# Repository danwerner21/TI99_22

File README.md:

# Texas Instruments TI99/4A Clone(ish) Project

Note that this is not a fully tested project at this point. . . .

This is based Rob Krenicki's design that is based on the HackMac KiCAD schematics.  I have made several changes to the original design including:

* Placing 32K of 16bit wide fast ram on the board to fully populate the address space
* Placing an EPROM on the main board that can be used as an on-board cartridge ROM
* adding a header to allow a microcontroller to replace the GROM chips (hopefully this can be moved on-board soon)
* replacing the video DRAM with SRAM
* Updating the Keyboard header to support a soft caps lock switch on the keyboard PCB
* designing a Cherry MX keyboard
* adding headers for the GROM and expansion port to support riser cards for these ports

If there are any questions, I can be reached at vic2020Dan at gmail dot com.

## ToDo
* Cleanup/Documentation
Possible Future Thoughts:
* Redo the Board in an ATX form factor with PEB slots on board
* Add Support for the Pico9918 on-board
* Add Support for a Tang Nano FPGA TMS9918 replacement 
* Add Hex-bus port
* Add a DIN 5-pin Composite video/Audio out. 
* Add built in speech synthesis
* Clone Disk IO card
* Relocate all the ports to the back of the motherboard

* It has been suggested that we also have a console style version of the next revision as not everyone has a desire for a larger PE style machine
* Also perhaps add some keys to the keyboard

## DIP Switch Settings
The DIP switch on the main board allows one to configure which bank areas are populated with RAM.

RAM0 enables RAM to addresses >2000-3FFF (Lo Memory Expansion)
RAM1 enables RAM to addresses >A000-BFFF (Hi Memory Expansion)
RAM2 enables RAM to addresses >C000-DFFF (Hi Memory Expansion)
RAM3 enables RAM to addresses >E000-FFFF  (Hi Memory Expansion)
RAM4 enables RAM to addresses >8000-83FF (Normal TI Scratch Pad RAM)

Note that I have never actually tested off-board 8 bit RAM, so this is new territory and might need some debugging 😊   
also on-board RAM is 16 bit – so all of those external RAM sources will be slower. 

## Bugs
* on rev 0.95 R36-40 are listed as 100K ohm, they are actually 100 ohm
* on rev 0.95 the joystick and cassette connectors are mirrored and need to be mounted on the bottom side of the board to function
* Both of these are corrected in 0.96

* The reset button J1 should be attached to pin 5 of U1 not Pin 4

## Bill of Materials
### Console
Qty|Reference(s)|Part
---|------------|----
6|C1, C9, C11, C58, C73, C75|0.001uF
1|C2|22pF
3|C3, C5, C59|22uF
12|C4, C7, C13, C14, C20, C54, C55, C62, C64, C68, C71, C74|0.1uF
1|C6|1uF
7|C8, C52, C63, C65, C66, C67, C72|0.01uF
1|C10|100uF
1|C12|0.01uF
7|C15, C16, C17, C19, C21, C22, C60|100uF
30|C18, C23, C24, C25, C26, C27, C28, C29, C30, C31, C32, C33, C34, C35, C36, C37, C38, C39, C40, C41, C42, C43, C44, C45, C46, C47, C48, C49, C50, C51|0.1uF
1|C53|100uF
1|C56|12pF
1|C57|56pF
1|C61|220uF
1|C69|220pF
1|C70|0.022uF
2|CR1, CR4|1N4148
2|CR2, CR3|1N914B
1|D1|LED
1|J1|Connector PinHeader 2.54mm:PinHeader 1x02 P2.54mm Vertical
1|J2|Connector PinHeader 2.54mm:PinHeader 1x02 P2.54mm Vertical
1|J3|TerminalBlock RND:TerminalBlock RND 205-00278 1x04 P5.00mm Vertical
1|J4|Connector PinHeader 2.54mm:PinHeader 1x16 P2.54mm Vertical
2|J5, J6|Connector PinHeader 2.54mm:PinHeader 1x03 P2.54mm Vertical
1|J7|Connector PinHeader 2.54mm:PinHeader 1x03 P2.54mm Vertical
1|J8|Connector PinHeader 2.54mm:PinHeader 1x02 P2.54mm Vertical
1|J9|Connector PinHeader 2.54mm:PinHeader 1x02 P2.54mm Vertical
1|J10|Connector Dsub:DSUB-9 Female Horizontal P2.77x2.84mm EdgePinOffset4.94mm Housed MountingHolesOffset7.48mm
1|J11|Connector PinHeader 2.54mm:PinHeader 1x18 P2.54mm Vertical
1|J12|Connector PinHeader 2.54mm:PinHeader 2x22 P2.54mm Vertical
1|J13|WernerCustomLibrary:44 Pin Card Edge
1|J14|Library:CardEdge 34Pin 2.54mm Vertical
1|J15|Connector PinHeader 2.54mm:PinHeader 2x18 P2.54mm Vertical
1|J16|Connector PinSocket 2.54mm:PinSocket 1x03 P2.54mm Vertical
1|J17|Connector PinSocket 2.54mm:PinSocket 1x03 P2.54mm Vertical
1|J18|Connector Dsub:DSUB-9 Female Horizontal P2.77x2.84mm EdgePinOffset4.94mm Housed MountingHolesOffset7.48mm
1|L1|0.33uH
2|L4, L5|6.8uH
1|L7|5.8uH
1|L8|INDUCTOR (Ferrite BEAD)
7|L10, L11, L12, L13, L14, L15, L16|8.2uH
3|Q1, Q3, Q4|TIS92
1|Q2|2N3904
1|R1|150k
7|R2, R9, R11, R18, R34, R35, R46|1k
1|R3|12k
1|R4|47k
4|R5, R6, R7, R8|22
5|R10, R26, R45, R52, R53|4.7k
5|R12, R13, R14, R15, R16|1K
3|R17, R48, R50|2.2k
2|R19, R30|470
1|R20|270
1|R21|1.5k x 9 SIP bussed
1|R22|361
3|R23, R73, R75|5.6k
2|R24, R27|10
1|R25|150
1|R28|470k
1|R29|0
2|R31, R33|75
1|R32|470
4|R41, R42, R43, R44|62
1|R47|3.3k
9|R36, R37, R38, R39, R40, R49, R51, R54, R56|100
1|R55|330
1|R57|10k
1|R58|6.8k
1|R59|39k
1|R60|6.8k
4|R61, R62, R67, R68|1K
1|R63|120k
1|R64|2.7k
3|R65, R66, R76|220
1|R69|10K
1|R70|9.1k
2|R71, R72|10k
1|R74|5.6K
1|R77|15
2|RN1, RN2|10K x 9 SIP Bussed
1|SW1|DIP switchx05
1|SW2|Pin Header 01x02 Male
1|U1|TMS9904 (note this needs to be a 9904 not 9904ANL.  If the 9904ANL is used, Y1 needs to be substituted with 12Mhz, L1 needs to be substituted with 3.3uh and C2 needs to be substituted with 50pf)
1|U2|TMS9900
4|U3, U15, U22, U24|74LS04
2|U4, U9|74LS32
2|U5, U8|74LS138
1|U6|74LS03
1|U7|74LS08
3|U10, U14, U18|74LS00
2|U11, U41|74LS244
1|U12|74LS373
1|U13|74LS245
1|U16|74LS74
1|U17|74LS194
1|U19|LM2901
1|U20|LM7905 TO220
1|U21|LM2903
3|U26, U27, U28|TMC0430
3|U29, U30, U37|HM62256BLP
2|U31, U32|27C64
1|U33|SN76489
1|U34|TMS9918
3|U35, U36, U38|74LS574
1|U39|TMS9901
1|U40|74LS156
2|U42, U43|74LS367
1|U44|74LS379
1|U45|27C010
1|U46|RC4558
1|U47|74LS06
2|U48, U49|TIL119
1|Y1|48.000 MHz Crystal
1|Y2|10.7MHz Crystal

# Keyboard
Qty|Reference(s)|Value|Part
---|------------|-----|----
1|C1|0.1uF|Capacitor
1|D1|LED|LED
1|D2|LED|LED
1|J1|Pin Header 1x18 male|Pin Header 1x18 male
2|R1, R2|470 ohm|Resistor
1|R3|1K ohm|Resistor
48|SW1-SW48|Mechanical Switch|Cherry MX Switch (or compatible)
1|U1|ATtiny13A-P|IC
1|U2|74LS125|IC
3||Switch Stabilizer 2.25|
1||Switch Stabilizer 6.25|
1||Optional Alignment frame (will need modified)|
|||
|Stabilizers (frame not used):|https://www.amazon.com/Genuine-Cherry-PCB-Snap-Stabilizers/dp/B085T8QZJC|
|Stabilizers (Frame used)|https://www.amazon.com/dp/B082X4V9VC|
|Frame:|https://www.amazon.com/gp/product/B07MMB33WG|

# Cartridge Riser
Qty|Reference(s)|Part|Type
---|------------|----|----
1|J1|Pin Header 01x18 Male|Pin Header 01x18 Male
1|J2|36 Pin Edge Connector|CONN EDGE DUAL FMALE 36POS 0.100 spacing

# IO Riser
Qty|Reference(s)|Part|Type
---|------------|----|----
1|J1|Pin Header 2x22 Male|Pin Header 2x22 Male

# UNICORN BOARD
Qty|Reference(s)|Part|Type
---|------------|----|----
1|J1|Pin Header Socket 01x16 Female Right Angle|Pin Header Socket 01x16 Female Right Angle
4|U1-U4|Level Shifter|https://www.amazon.com/KeeYees-Channels-Converter-Bi-Directional-Shifter/dp/B07LG646VS
1|U5|ESP32 Devkit|https://www.amazon.com/Development-Microcontroller-Integrated-Antenna-Amplifiers/dp/B09GK74F7N

## License

The original project was licensed under the Creative Commons - Attribution - ShareAlike 3.0 License

## Attribution

This board was derrived from works by, uses design elements from, or contains sofware writen by the following:
* Rob Krenicki (https://github.com/rkrenicki/TI99-Motherboard)
* HackMac (https://bitbucket.org/hackmac/ti-schematics/wiki/Home)

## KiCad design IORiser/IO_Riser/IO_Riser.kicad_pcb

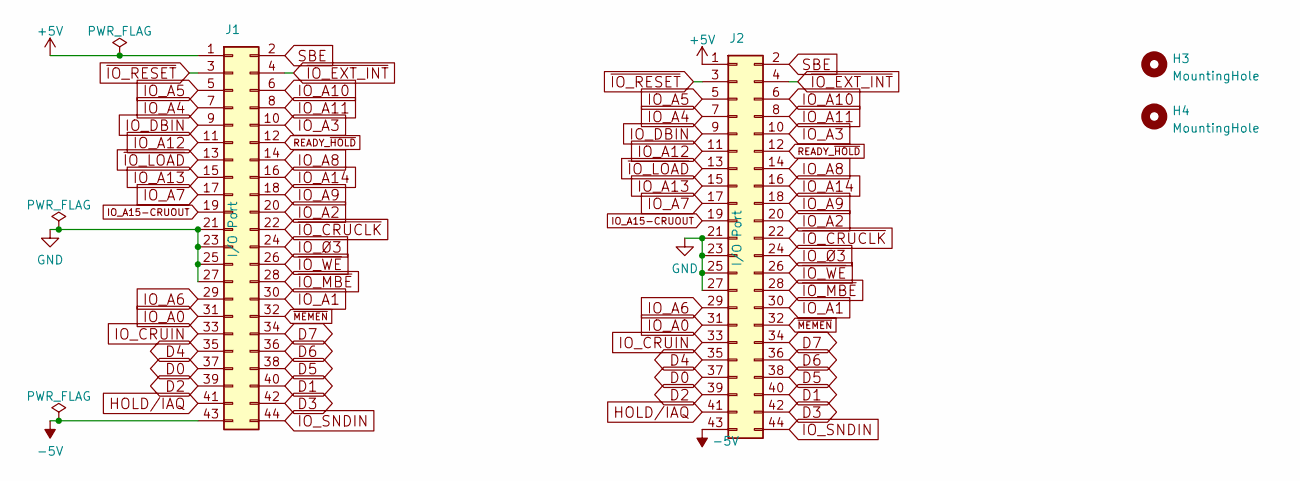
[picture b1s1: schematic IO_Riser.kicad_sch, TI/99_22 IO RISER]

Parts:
H3, H4: MountingHole; MountingHole_3.2mm_M3
J1: I/O Port; PinHeader_2x22_P2.54mm_Vertical
J2: I/O Port; 44 Pin Card Edge

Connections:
+5V: J1.1, J2.1
-5V: J1.43, J2.43
D0: J1.37, J2.37
D1: J1.40, J2.40
D2: J1.39, J2.39
D3: J1.42, J2.42
D4: J1.35, J2.35
D5: J1.38, J2.38
D6: J1.36, J2.36
D7: J1.34, J2.34
GND: J1.21, J1.23, J1.25, J1.27, J2.21, J2.23, J2.25, J2.27
HOLD/IAQ: J1.41, J2.41
IO_A0: J1.31, J2.31
IO_A1: J1.30, J2.30
IO_A2: J1.20, J2.20
IO_A3: J1.10, J2.10
IO_A4: J1.7, J2.7
IO_A5: J1.5, J2.5
IO_A6: J1.29, J2.29
IO_A7: J1.17, J2.17
IO_A8: J1.14, J2.14
IO_A9: J1.18, J2.18
IO_A10: J1.6, J2.6
IO_A11: J1.8, J2.8
IO_A12: J1.11, J2.11
IO_A13: J1.15, J2.15
IO_A14: J1.16, J2.16
IO_A15-CRUOUT: J1.19, J2.19
IO_CRUIN: J1.33, J2.33
IO_DBIN: J1.9, J2.9
IO_SNDIN: J1.44, J2.44
IO_Ø3: J1.24, J2.24
READY_~HOLD: J1.12, J2.12
SBE: J1.2, J2.2
~IO_CRUCLK: J1.22, J2.22
~IO_EXT_INT: J1.4, J2.4
~IO_LOAD: J1.13, J2.13
~IO_MBE: J1.28, J2.28
~IO_RESET: J1.3, J2.3
~IO_WE: J1.26, J2.26
~MEMEN: J1.32, J2.32

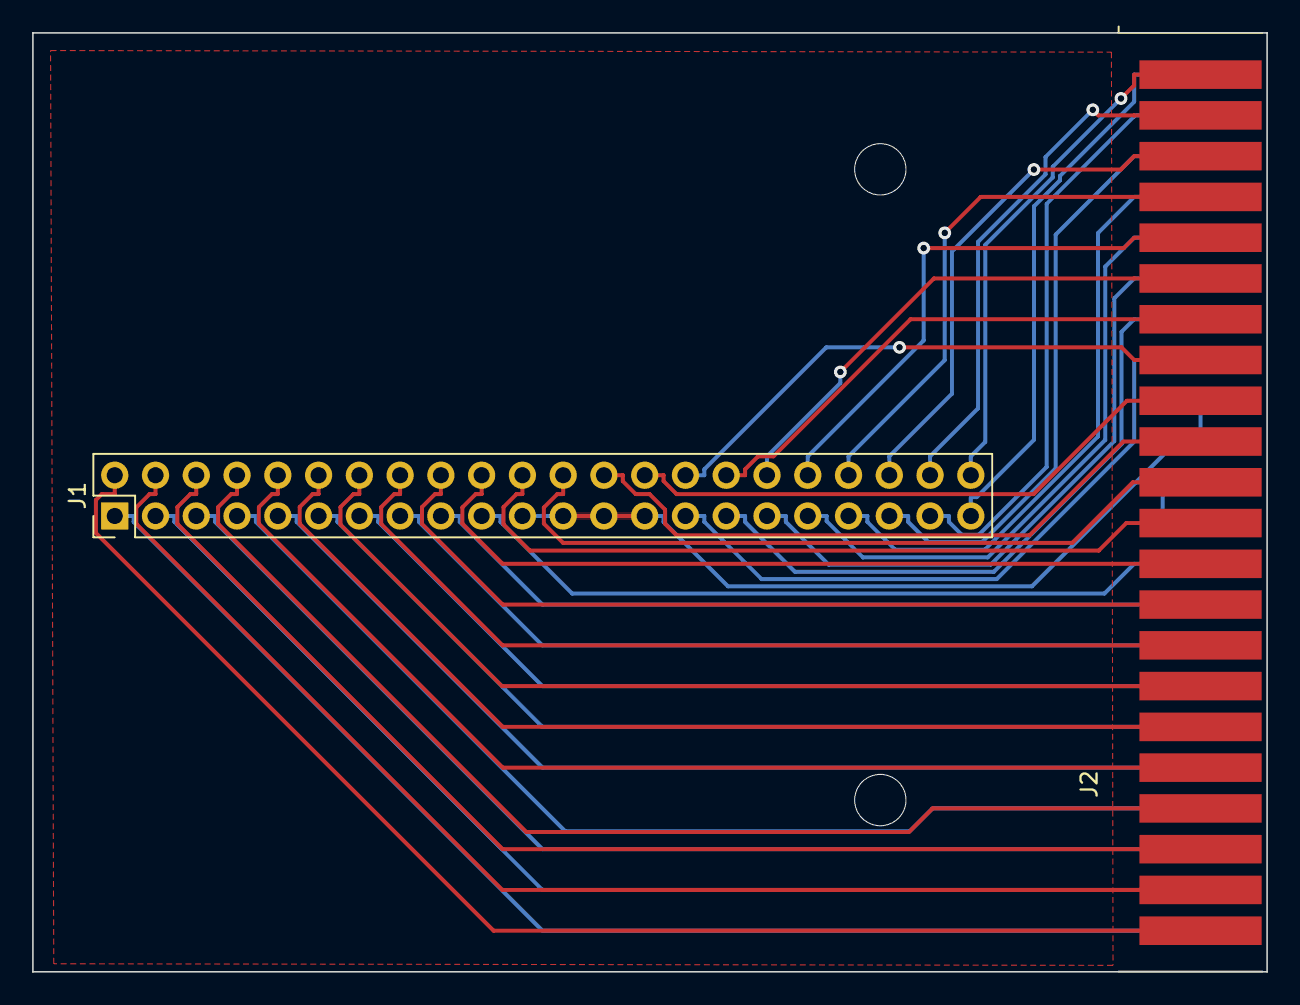
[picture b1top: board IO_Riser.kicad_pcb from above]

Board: 2 copper layers, 76.9 x 58.5 mm, 4 parts (0 on the bottom side), 41 nets.

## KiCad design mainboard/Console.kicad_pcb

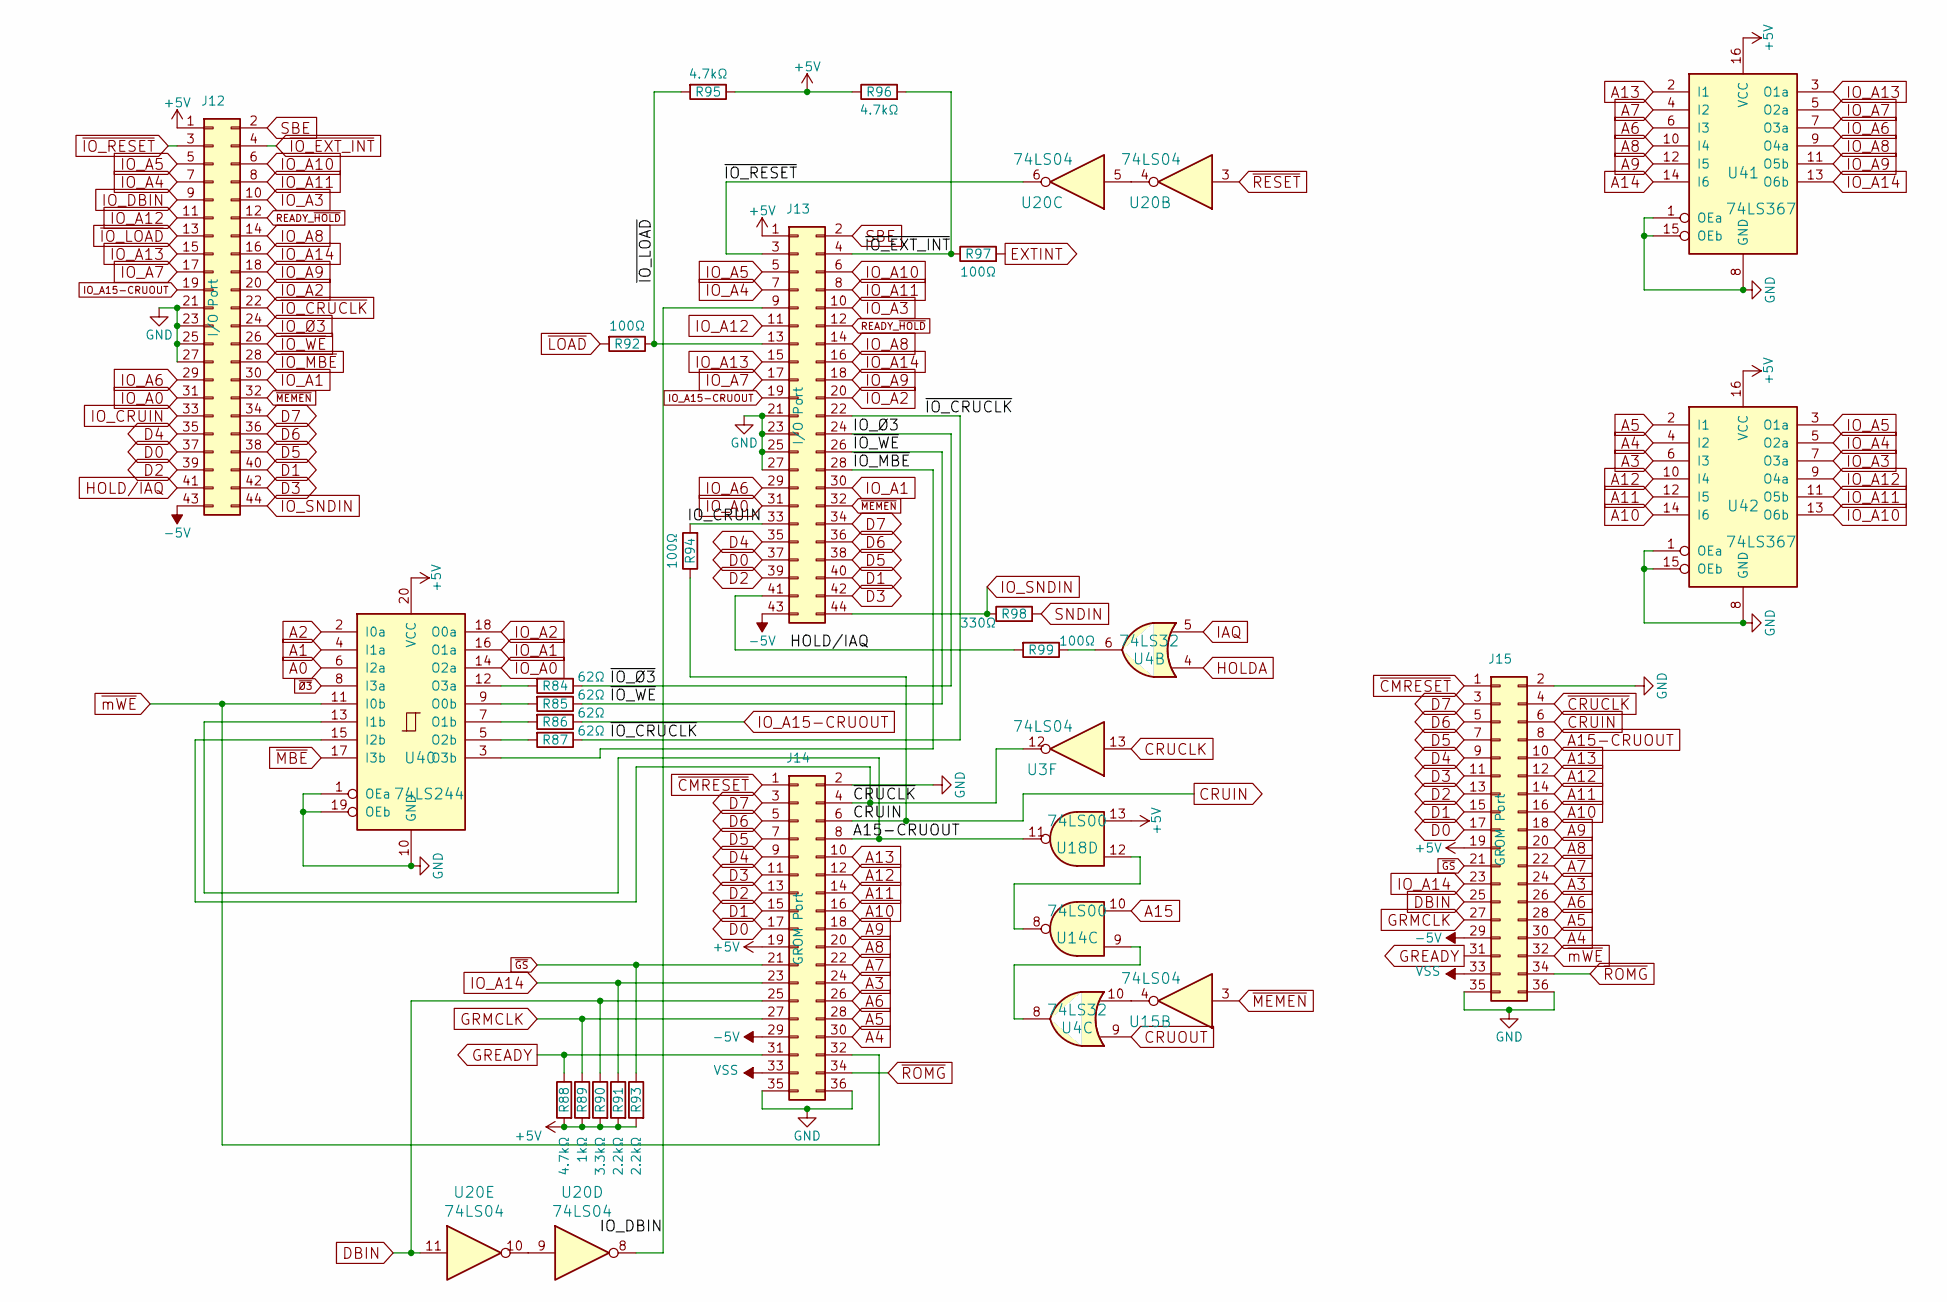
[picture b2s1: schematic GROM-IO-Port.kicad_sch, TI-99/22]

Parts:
J12: I/O Port; PinHeader_2x22_P2.54mm_Vertical
J13: I/O Port; 44 Pin Card Edge
J14: GROM Port; CardEdge_34Pin_2.54mm_Vertical
J15: GROM Port; PinHeader_2x18_P2.54mm_Vertical
R84, R85, R86, R87: 62Ω; R_Axial_DIN0207_L6.3mm_D2.5mm_P7.62mm_Horizontal
R88, R95, R96: 4.7kΩ; R_Axial_DIN0207_L6.3mm_D2.5mm_P7.62mm_Horizontal
R89: 1kΩ; R_Axial_DIN0207_L6.3mm_D2.5mm_P7.62mm_Horizontal
R90: 3.3kΩ; R_Axial_DIN0207_L6.3mm_D2.5mm_P7.62mm_Horizontal
R91, R93: 2.2kΩ; R_Axial_DIN0207_L6.3mm_D2.5mm_P7.62mm_Horizontal
R92, R94, R97, R99: 100Ω; R_Axial_DIN0207_L6.3mm_D2.5mm_P7.62mm_Horizontal
R98: 330Ω; R_Axial_DIN0207_L6.3mm_D2.5mm_P7.62mm_Horizontal
U3, U15, U20: 74LS04; DIP-14_W7.62mm_Socket_LongPads
U4: 74LS32; DIP-14_W7.62mm_Socket_LongPads
U14, U18: 74LS00; DIP-14_W7.62mm_Socket_LongPads
U40: 74LS244; DIP-20_W7.62mm_Socket_LongPads
U41, U42: 74LS367; DIP-16_W7.62mm_Socket_LongPads

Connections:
+5V: J12.1, J13.1, J14.19, J15.19, R88.2, R89.2, R90.2, R91.2, R93.2, R95.1, R96.1, U18.13, U40.20 (VCC), U41.16 (VCC), U42.16 (VCC); also elsewhere on the board
-5V: J12.43, J13.43, J14.29, J15.29; also elsewhere on the board
A0: U40.6 (I2a); also elsewhere on the board
A1: U40.4 (I1a); also elsewhere on the board
A2: U40.2 (I0a); also elsewhere on the board
A3: J14.24, J15.24, U42.6 (I3); also elsewhere on the board
A4: J14.30, J15.30, U42.4 (I2); also elsewhere on the board
A5: J14.28, J15.28, U42.2 (I1); also elsewhere on the board
A6: J14.26, J15.26, U41.6 (I3); also elsewhere on the board
A7: J14.22, J15.22, U41.4 (I2); also elsewhere on the board
A8: J14.20, J15.20, U41.10 (I4); also elsewhere on the board
A9: J14.18, J15.18, U41.12 (I5); also elsewhere on the board
A10: J14.16, J15.16, U42.14 (I6); also elsewhere on the board
A11: J14.14, J15.14, U42.12 (I5); also elsewhere on the board
A12: J14.12, J15.12, U42.10 (I4); also elsewhere on the board
A13: J14.10, J15.10, U41.2 (I1); also elsewhere on the board
A14: U41.14 (I6); also elsewhere on the board
A15: U14.10; also elsewhere on the board
A15-CRUOUT: J14.8, J15.8, U18.11, U40.13 (I1b); also elsewhere on the board
CRUCLK: U3.13; also elsewhere on the board
CRUIN: J14.6, J15.6, R94.1; also elsewhere on the board
CRUOUT: U4.9; also elsewhere on the board
D0: J12.37, J13.37, J14.17, J15.17; also elsewhere on the board
D1: J12.40, J13.40, J14.15, J15.15; also elsewhere on the board
D2: J12.39, J13.39, J14.13, J15.13; also elsewhere on the board
D3: J12.42, J13.42, J14.11, J15.11; also elsewhere on the board
D4: J12.35, J13.35, J14.9, J15.9; also elsewhere on the board
D5: J12.38, J13.38, J14.7, J15.7; also elsewhere on the board
D6: J12.36, J13.36, J14.5, J15.5; also elsewhere on the board
D7: J12.34, J13.34, J14.3, J15.3; also elsewhere on the board
DBIN: J14.25, J15.25, R90.1, U20.11; also elsewhere on the board
EXTINT: R97.2; also elsewhere on the board
GREADY: J14.31, J15.31, R88.1; also elsewhere on the board
GRMCLK: J14.27, J15.27, R89.1; also elsewhere on the board
HOLDA: U4.4; also elsewhere on the board
IAQ: U4.5; also elsewhere on the board
IO_A0: J12.31, J13.31, U40.14 (O2a)
IO_A1: J12.30, J13.30, U40.16 (O1a)
IO_A2: J12.20, J13.20, U40.18 (O0a)
IO_A3: J12.10, J13.10, U42.7 (O3a); also elsewhere on the board
IO_A4: J12.7, J13.7, U42.5 (O2a); also elsewhere on the board
IO_A5: J12.5, J13.5, U42.3 (O1a); also elsewhere on the board
IO_A6: J12.29, J13.29, U41.7 (O3a)
IO_A7: J12.17, J13.17, U41.5 (O2a)
IO_A8: J12.14, J13.14, U41.9 (O4a)
IO_A9: J12.18, J13.18, U41.11 (O5b)
IO_A10: J12.6, J13.6, U42.13 (O6b)
IO_A11: J12.8, J13.8, U42.11 (O5b)
IO_A12: J12.11, J13.11, U42.9 (O4a)
IO_A13: J12.15, J13.15, U41.3 (O1a)
IO_A14: J12.16, J13.16, J14.23, J15.23, R91.1, U41.13 (O6b); also elsewhere on the board
IO_A15-CRUOUT: J12.19, J13.19, R86.1
IO_CRUIN: J12.33, J13.33, R94.2
IO_DBIN: J12.9, J13.9, U20.8
IO_SNDIN: J12.44, J13.44, R98.1
IO_Ø3: J12.24, J13.24, R84.1
unnamed: R84.2, U40.12 (O3a)
unnamed: R85.2, U40.9 (O0b)
unnamed: R86.2, U40.7 (O1b)
unnamed: R87.2, U40.5 (O2b)
unnamed: R99.1, U4.6
unnamed: U14.8, U18.12
unnamed: U4.8, U14.9
unnamed: U4.10, U15.4
unnamed: U20.4, U20.5
unnamed: U20.9, U20.10
READY_~HOLD: J12.12, J13.12; also elsewhere on the board
SBE: J12.2, J13.2; also elsewhere on the board
SNDIN: R98.2; also elsewhere on the board
VRAM_BANK: J12.21, J12.23, J12.25, J12.27, J13.21, J13.23, J13.25, J13.27, J14.2, J14.35, J14.36, J15.2, J15.35, J15.36, U40.1 (OEa), U40.10 (GND), U40.19 (OEb), U41.1 (OEa), U41.8 (GND), U41.15 (OEb), U42.1 (OEa), U42.8 (GND), U42.15 (OEb); also elsewhere on the board
VSS: J14.33, J15.33; also elsewhere on the board
~CMRESET: J14.1, J15.1; also elsewhere on the board
~CRUCLK: J14.4, J15.4, U3.12, U40.15 (I2b)
~GS: J14.21, J15.21, R93.1; also elsewhere on the board
~IO_CRUCLK: J12.22, J13.22, R87.1
~IO_EXT_INT: J12.4, J13.4, R96.2, R97.1
~IO_LOAD: J12.13, J13.13, R92.1, R95.2
~IO_MBE: J12.28, J13.28, U40.3 (O3b)
~IO_RESET: J12.3, J13.3, U20.6
~IO_WE: J12.26, J13.26, R85.1
~LOAD: R92.2; also elsewhere on the board
~MBE: U40.17 (I3b); also elsewhere on the board
~MEMEN: J12.32, J13.32, U15.3; also elsewhere on the board
~RESET: U20.3; also elsewhere on the board
~ROMG: J14.34, J15.34; also elsewhere on the board
~mWE: J14.32, J15.32, U40.11 (I0b); also elsewhere on the board
~Ø3: U40.8 (I3a); also elsewhere on the board

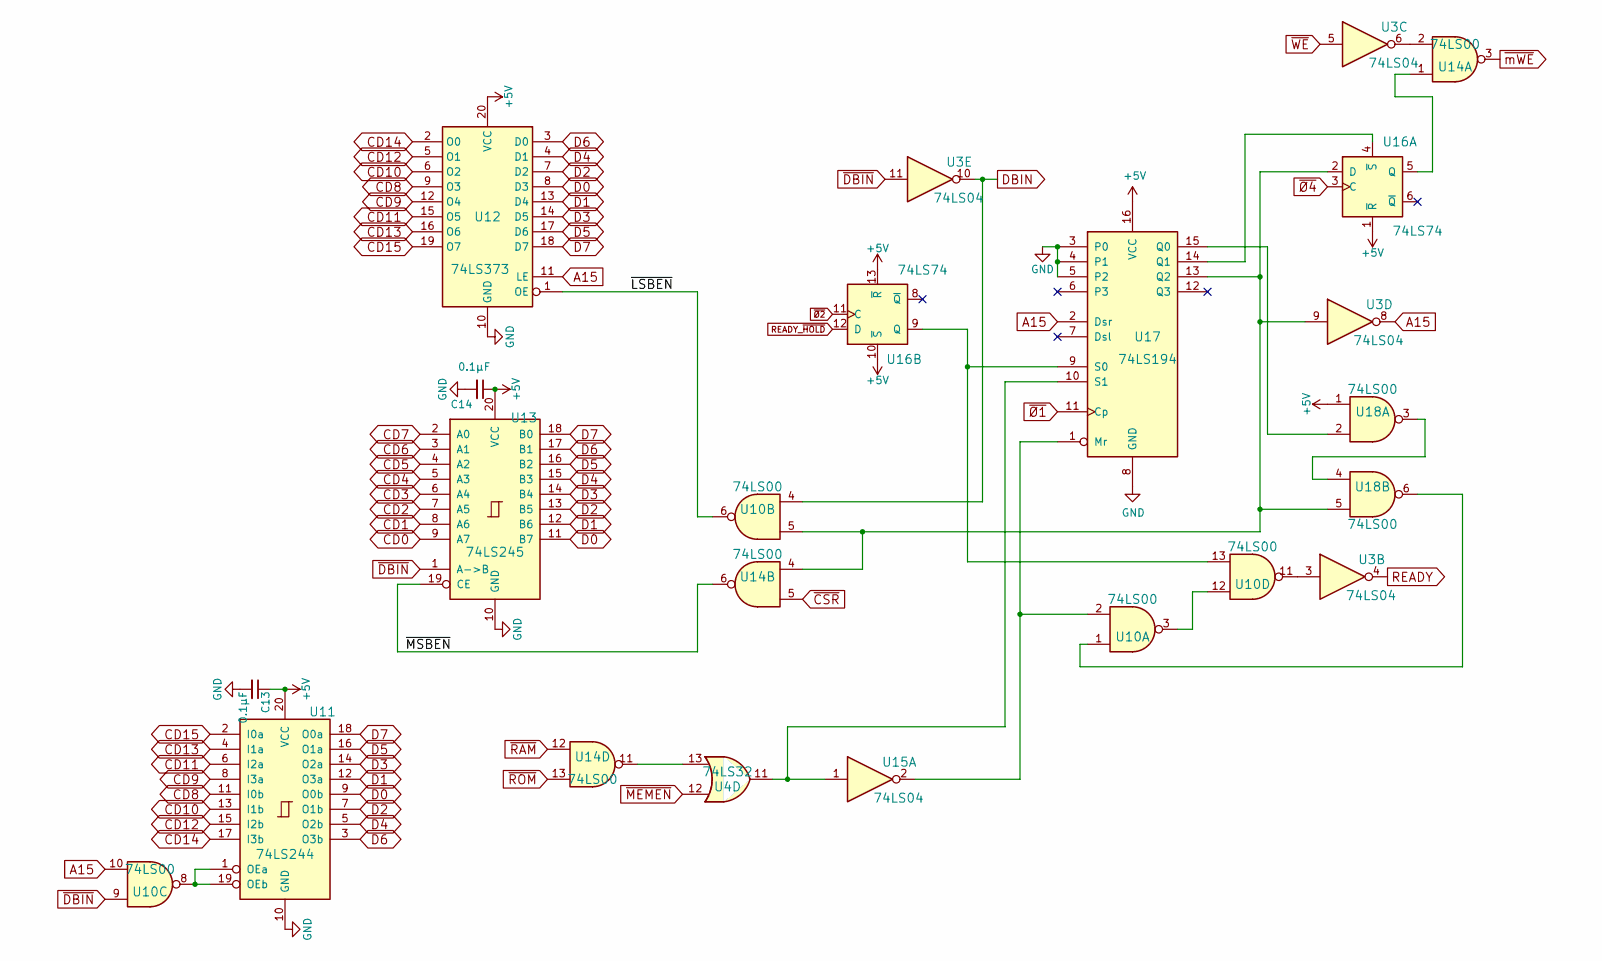
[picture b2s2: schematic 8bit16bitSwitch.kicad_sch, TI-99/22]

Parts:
C13, C14: 0.1µF; C_Rect_L7.0mm_W2.0mm_P5.00mm
U3, U15: 74LS04; DIP-14_W7.62mm_Socket_LongPads
U4: 74LS32; DIP-14_W7.62mm_Socket_LongPads
U10, U14, U18: 74LS00; DIP-14_W7.62mm_Socket_LongPads
U11: 74LS244; DIP-20_W7.62mm_Socket_LongPads
U12: 74LS373; DIP-20_W7.62mm_Socket_LongPads
U13: 74LS245; DIP-20_W7.62mm_Socket_LongPads
U16: 74LS74; DIP-14_W7.62mm_Socket_LongPads
U17: 74LS194; DIP-16_W7.62mm_Socket_LongPads

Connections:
+5V: C13.1, C14.1, U11.20 (VCC), U12.20 (VCC), U13.20 (VCC), U16.1 (~R), U16.10 (~S), U16.13 (~R), U17.16 (VCC), U18.1; also elsewhere on the board
/8Bit16BitSwitch/~LSBEN: U10.6, U12.1 (OE)
/8Bit16BitSwitch/~MSBEN: U13.19 (CE), U14.6
A15: U3.8, U10.10, U12.11 (LE), U17.2 (Dsr); also elsewhere on the board
CD0: U13.9 (A7); also elsewhere on the board
CD1: U13.8 (A6); also elsewhere on the board
CD2: U13.7 (A5); also elsewhere on the board
CD3: U13.6 (A4); also elsewhere on the board
CD4: U13.5 (A3); also elsewhere on the board
CD5: U13.4 (A2); also elsewhere on the board
CD6: U13.3 (A1); also elsewhere on the board
CD7: U13.2 (A0); also elsewhere on the board
CD8: U11.11 (I0b), U12.9 (O3); also elsewhere on the board
CD9: U11.8 (I3a), U12.12 (O4); also elsewhere on the board
CD10: U11.13 (I1b), U12.6 (O2); also elsewhere on the board
CD11: U11.6 (I2a), U12.15 (O5); also elsewhere on the board
CD12: U11.15 (I2b), U12.5 (O1); also elsewhere on the board
CD13: U11.4 (I1a), U12.16 (O6); also elsewhere on the board
CD14: U11.17 (I3b), U12.2 (O0); also elsewhere on the board
CD15: U11.2 (I0a), U12.19 (O7); also elsewhere on the board
D0: U11.9 (O0b), U12.8 (D3), U13.11 (B7); also elsewhere on the board
D1: U11.12 (O3a), U12.13 (D4), U13.12 (B6); also elsewhere on the board
D2: U11.7 (O1b), U12.7 (D2), U13.13 (B5); also elsewhere on the board
D3: U11.14 (O2a), U12.14 (D5), U13.14 (B4); also elsewhere on the board
D4: U11.5 (O2b), U12.4 (D1), U13.15 (B3); also elsewhere on the board
D5: U11.16 (O1a), U12.17 (D6), U13.16 (B2); also elsewhere on the board
D6: U11.3 (O3b), U12.3 (D0), U13.17 (B1); also elsewhere on the board
D7: U11.18 (O0a), U12.18 (D7), U13.18 (B0); also elsewhere on the board
DBIN: U3.10, U10.4; also elsewhere on the board
unnamed: U10.1, U18.6
unnamed: U10.2, U15.2, U17.1 (Mr)
unnamed: U3.9, U10.5, U14.4, U16.2 (D), U17.13 (Q2), U18.5
unnamed: U10.8, U11.1 (OEa), U11.19 (OEb)
unnamed: U3.3, U10.11
unnamed: U10.3, U10.12
unnamed: U10.13, U16.9 (Q), U17.9 (S0)
unnamed: U14.1, U16.5 (Q)
unnamed: U3.6, U14.2
unnamed: U4.13, U14.11
unnamed: U4.11, U15.1, U17.10 (S1)
unnamed: U16.4 (~S), U17.14 (Q1)
unnamed: U17.15 (Q0), U18.2
unnamed: U18.3, U18.4
READY: U3.4; also elsewhere on the board
READY_~HOLD: U16.12 (D); also elsewhere on the board
VRAM_BANK: C13.2, C14.2, U11.10 (GND), U12.10 (GND), U13.10 (GND), U17.3 (P0), U17.4 (P1), U17.5 (P2), U17.8 (GND); also elsewhere on the board
~CSR: U14.5; also elsewhere on the board
~DBIN: U3.11, U10.9, U13.1 (A->B); also elsewhere on the board
~MEMEN: U4.12; also elsewhere on the board
~RAM: U14.12; also elsewhere on the board
~ROM: U14.13; also elsewhere on the board
~WE: U3.5; also elsewhere on the board
~mWE: U14.3; also elsewhere on the board
~Ø1: U17.11 (Cp); also elsewhere on the board
~Ø2: U16.11 (C); also elsewhere on the board
~Ø4: U16.3 (C); also elsewhere on the board

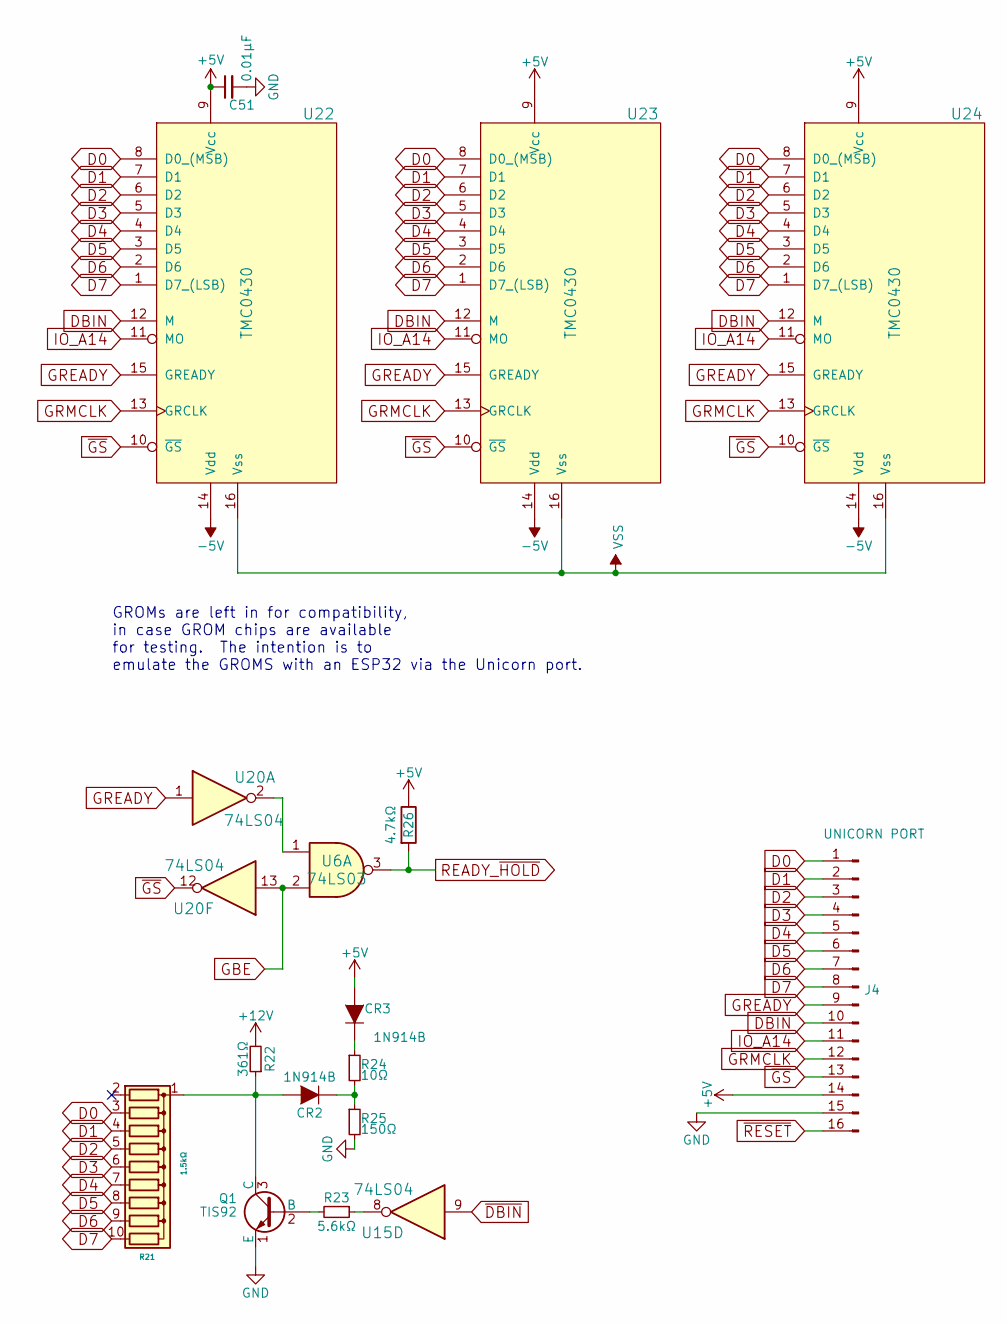
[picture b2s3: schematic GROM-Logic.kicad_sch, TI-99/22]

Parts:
C51: 0.01µF; C_Rect_L7.0mm_W2.0mm_P5.00mm
CR2, CR3: 1N914B; D_A-405_P7.62mm_Horizontal
J4: UNICORN PORT; PinHeader_1x16_P2.54mm_Vertical
Q1: TIS92; TO-92_HandSolder
R21: 1.5kΩ; R_Array_SIP10
R22: 361Ω; R_Axial_DIN0207_L6.3mm_D2.5mm_P7.62mm_Horizontal
R23: 5.6kΩ; R_Axial_DIN0207_L6.3mm_D2.5mm_P7.62mm_Horizontal
R24: 10Ω; R_Axial_DIN0207_L6.3mm_D2.5mm_P7.62mm_Horizontal
R25: 150Ω; R_Axial_DIN0207_L6.3mm_D2.5mm_P7.62mm_Horizontal
R26: 4.7kΩ; R_Axial_DIN0207_L6.3mm_D2.5mm_P7.62mm_Horizontal
U6: 74LS03; DIP-14_W7.62mm_Socket_LongPads
U15, U20: 74LS04; DIP-14_W7.62mm_Socket_LongPads
U22, U23, U24: TMC0430; DIP-16_W7.62mm_Socket_LongPads

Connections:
+5V: C51.1, CR3.2 (A), J4.14, R26.1, U22.9 (Vcc), U23.9 (Vcc), U24.9 (Vcc); also elsewhere on the board
+12V: R22.2; also elsewhere on the board
-5V: U22.14 (Vdd), U23.14 (Vdd), U24.14 (Vdd); also elsewhere on the board
D0: J4.1, R21.3 (R2), U22.8 (D0_(MSB)), U23.8 (D0_(MSB)), U24.8 (D0_(MSB)); also elsewhere on the board
D1: J4.2, R21.4 (R3), U22.7 (D1), U23.7 (D1), U24.7 (D1); also elsewhere on the board
D2: J4.3, R21.5 (R4), U22.6 (D2), U23.6 (D2), U24.6 (D2); also elsewhere on the board
D3: J4.4, R21.6 (R5), U22.5 (D3), U23.5 (D3), U24.5 (D3); also elsewhere on the board
D4: J4.5, R21.7 (R6), U22.4 (D4), U23.4 (D4), U24.4 (D4); also elsewhere on the board
D5: J4.6, R21.8 (R7), U22.3 (D5), U23.3 (D5), U24.3 (D5); also elsewhere on the board
D6: J4.7, R21.9 (R8), U22.2 (D6), U23.2 (D6), U24.2 (D6); also elsewhere on the board
D7: J4.8, R21.10 (R9), U22.1 (D7_(LSB)), U23.1 (D7_(LSB)), U24.1 (D7_(LSB)); also elsewhere on the board
DBIN: J4.10, U22.12 (M), U23.12 (M), U24.12 (M); also elsewhere on the board
GBE: U6.2, U20.13; also elsewhere on the board
GREADY: J4.9, U20.1, U22.15 (GREADY), U23.15 (GREADY), U24.15 (GREADY); also elsewhere on the board
GRMCLK: J4.12, U22.13 (GRCLK), U23.13 (GRCLK), U24.13 (GRCLK); also elsewhere on the board
IO_A14: J4.11, U22.11 (MO), U23.11 (MO), U24.11 (MO); also elsewhere on the board
unnamed: CR2.1 (K), R24.2, R25.1
unnamed: CR2.2 (A), Q1.3 (C), R21.1 (common), R22.1
unnamed: CR3.1 (K), R24.1
unnamed: Q1.2 (B), R23.2
unnamed: R23.1, U15.8
unnamed: U6.1, U20.2
READY_~HOLD: R26.2, U6.3; also elsewhere on the board
VRAM_BANK: C51.2, J4.15, Q1.1 (E), R25.2; also elsewhere on the board
VSS: U22.16 (Vss), U23.16 (Vss), U24.16 (Vss); also elsewhere on the board
~DBIN: U15.9; also elsewhere on the board
~GS: J4.13, U20.12, U22.10 (~GS), U23.10 (~GS), U24.10 (~GS); also elsewhere on the board
~RESET: J4.16; also elsewhere on the board

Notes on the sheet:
GROMs are left in for compatibility, in case GROM chips are available for testing. The intention is to emulate the GROMS with an ESP32 via the Unicorn port.

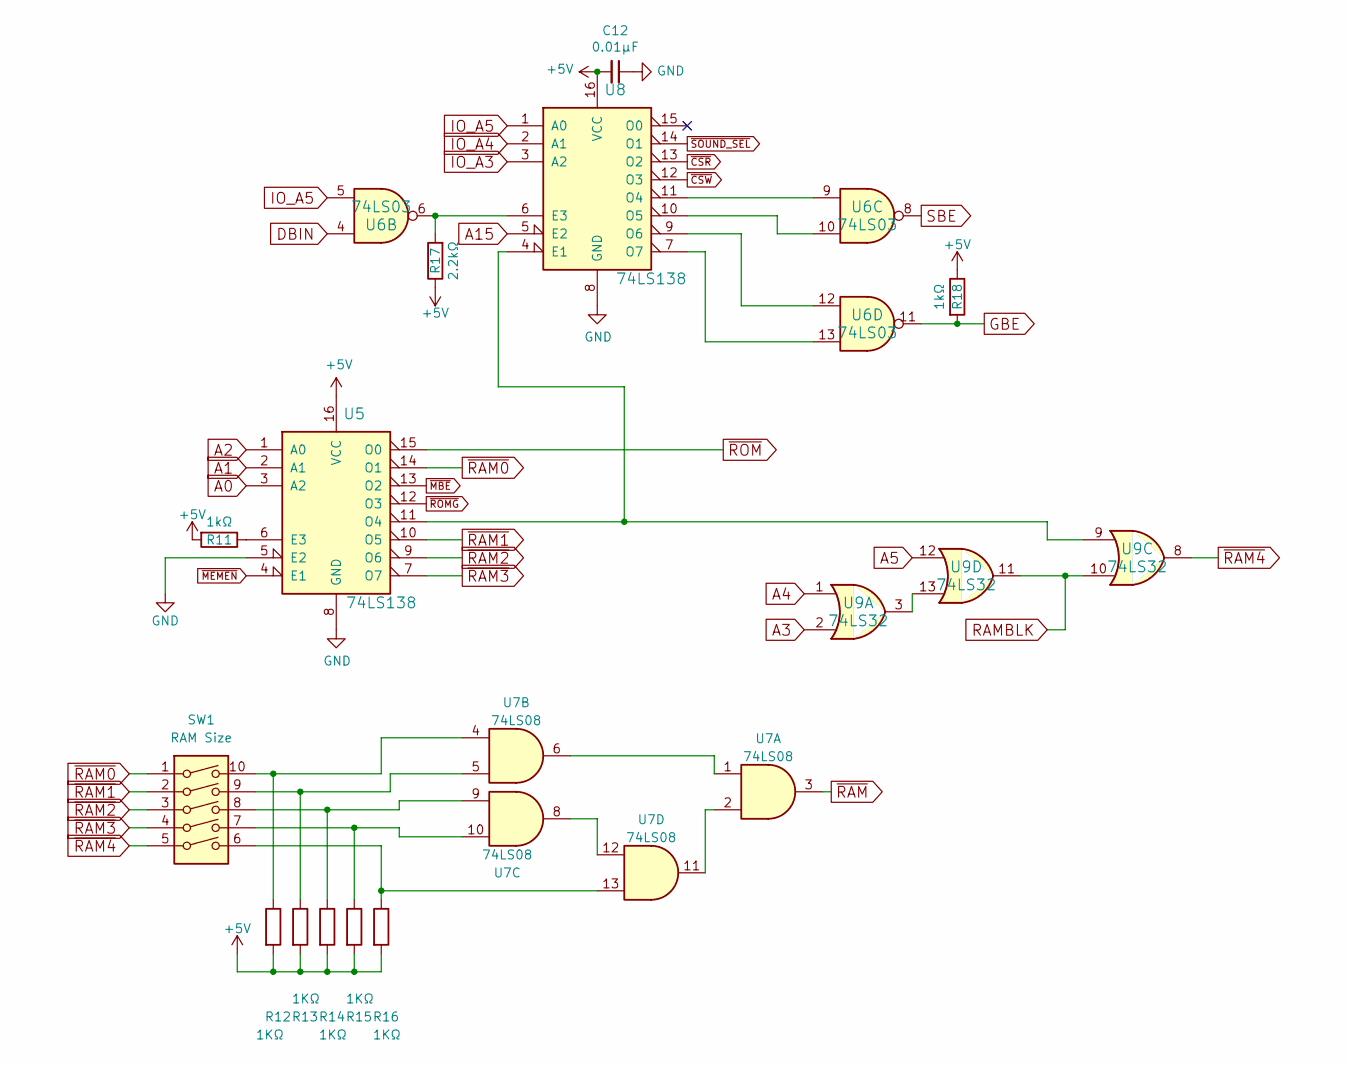
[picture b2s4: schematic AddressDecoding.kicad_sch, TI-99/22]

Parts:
C12: 0.01µF; C_Rect_L7.0mm_W2.0mm_P5.00mm
R11, R18: 1kΩ; R_Axial_DIN0207_L6.3mm_D2.5mm_P7.62mm_Horizontal
R12, R13, R14, R15, R16: 1KΩ; R_Axial_DIN0207_L6.3mm_D2.5mm_P7.62mm_Horizontal
R17: 2.2kΩ; R_Axial_DIN0207_L6.3mm_D2.5mm_P7.62mm_Horizontal
SW1: RAM Size; DIP-10_W7.62mm_Socket_LongPads
U5, U8: 74LS138; DIP-16_W7.62mm_Socket_LongPads
U6: 74LS03; DIP-14_W7.62mm_Socket_LongPads
U7: 74LS08; DIP-14_W7.62mm_Socket_LongPads
U9: 74LS32; DIP-14_W7.62mm_Socket_LongPads

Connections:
+5V: C12.2, R11.2, R12.2, R13.2, R14.2, R15.2, R16.2, R17.1, R18.1, U5.16 (VCC), U8.16 (VCC); also elsewhere on the board
A0: U5.3 (A2); also elsewhere on the board
A1: U5.2 (A1); also elsewhere on the board
A2: U5.1 (A0); also elsewhere on the board
A3: U9.2; also elsewhere on the board
A4: U9.1; also elsewhere on the board
A5: U9.12; also elsewhere on the board
A15: U8.5 (E2); also elsewhere on the board
DBIN: U6.4; also elsewhere on the board
GBE: R18.2, U6.11; also elsewhere on the board
IO_A3: U8.3 (A2); also elsewhere on the board
IO_A4: U8.2 (A1); also elsewhere on the board
IO_A5: U6.5, U8.1 (A0); also elsewhere on the board
unnamed: R11.1, U5.6 (E3)
unnamed: R12.1, SW1.10, U7.4
unnamed: R13.1, SW1.9, U7.5
unnamed: R14.1, SW1.8, U7.9
unnamed: R15.1, SW1.7, U7.10
unnamed: R16.1, SW1.6, U7.13
unnamed: R17.2, U6.6, U8.6 (E3)
unnamed: U5.11 (O4), U8.4 (E1), U9.9
unnamed: U6.9, U8.11 (O4)
unnamed: U6.10, U8.10 (O5)
unnamed: U6.12, U8.9 (O6)
unnamed: U6.13, U8.7 (O7)
unnamed: U7.1, U7.6
unnamed: U7.2, U7.11
unnamed: U7.8, U7.12
unnamed: U9.3, U9.13
RAMBLK: U9.10, U9.11; also elsewhere on the board
SBE: U6.8; also elsewhere on the board
VRAM_BANK: C12.1, U5.5 (E2), U5.8 (GND), U8.8 (GND); also elsewhere on the board
~CSR: U8.13 (O2); also elsewhere on the board
~CSW: U8.12 (O3); also elsewhere on the board
~MBE: U5.13 (O2); also elsewhere on the board
~MEMEN: U5.4 (E1); also elsewhere on the board
~RAM0: SW1.1, U5.14 (O1)
~RAM1: SW1.2, U5.10 (O5)
~RAM2: SW1.3, U5.9 (O6)
~RAM3: SW1.4, U5.7 (O7)
~RAM4: SW1.5, U9.8
~RAM: U7.3; also elsewhere on the board
~ROMG: U5.12 (O3); also elsewhere on the board
~ROM: U5.15 (O0); also elsewhere on the board
~SOUND_SEL: U8.14 (O1); also elsewhere on the board
